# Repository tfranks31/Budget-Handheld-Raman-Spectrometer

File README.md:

# Budget-Handheld-Raman-Spectrometer
An inexpensive DIY handheld Raman spectrometer! Ever want to make a handheld Raman spectrometer for under $300?
Probably not! However, matter is just about everywhere and makes up most of everything. It would be cool to have a 
device that tells you what something is made out of, and would be even cooler to build it yourself!

This repository serves as the main repository for this project, and contains source code, electrical schematics, CAD 
models, future plans, and documentation for it all.

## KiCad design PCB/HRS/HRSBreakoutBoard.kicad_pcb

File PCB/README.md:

# PCB design and electrical schematics
Here exists all PCB designs and electrical schematics for the handheld Raman spectrometer project.

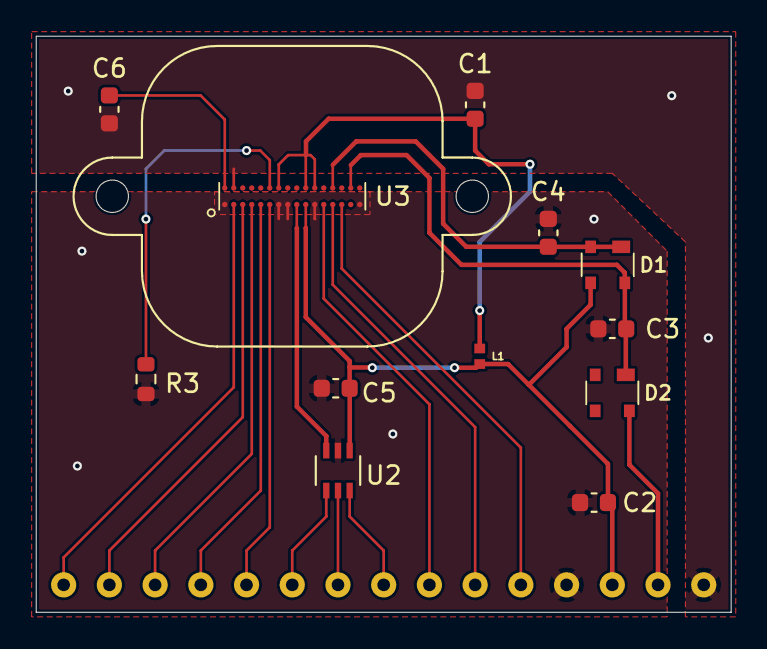
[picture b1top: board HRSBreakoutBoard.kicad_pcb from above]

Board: 2 copper layers, 38.6 x 32.0 mm, 13 parts (0 on the bottom side), 21 nets.

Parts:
C1, C2, C5, C6: 1.0uF; C_0603_1608Metric
C3, C4: 2.2uF; C_0603_1608Metric
D1, D2: BAT74,215; SOT143(B)
J1: Conn_01x15; Breakout Board Connector
L1: 600; BEADC1005X55N
R3: 56k; R_0603_1608Metric
U2: AD7476A; AD7476
U3: epc901; EPC901

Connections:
/AGND: C2.2, C3.1, C4.1, C5.1, J1.12, R3.2, U2.2 (GND), U3.1 (AGND), U3.7 (GND_OA), U3.8 (VIDEO_N), U3.11 (VIDEO_CM), U3.16 (AGND)
/CLR_DATA: J1.2, U3.3 (CLR_DATA)
/CLR_PIX: J1.4, U3.5 (CLR_PIX)
/DATA_RDY: J1.3, U3.4 (DATA_RDY)
/DGND: C1.1, C6.1, J1.15, U3.31 (DGND)
/PWR_DOWN: J1.1, U3.2 (PWR_DOWN)
/READ: J1.9, U3.12 (READ)
/SCL: J1.11, U3.14 (SCL)
/SCLK: J1.6, U2.4 (SCLK)
/SDA: J1.10, U3.13 (SDA)
/SDATA: J1.7, U2.5 (SDATA)
/SHUTTER: J1.5, U3.6 (SHUTTER)
/VDD: C1.2, L1.2, U3.22 (BW0), U3.23 (BW1), U3.26 (VDD)
/VDD_3V: C2.1, C5.2, D1.3, J1.13, L1.1, U2.1 (VDD), U3.10 (VDD_OA)
/VDD_5V: D2.4, J1.14
/VDD_5V0: C3.2, D1.4, D2.1, U3.18 (VDD_5V0)
/VDD_7V0: C4.2, D1.1, D1.2, U3.20 (VDD_7V0)
/VIDEO_P: U2.3 (VIN), U3.9 (VIDEO_P)
/~CS: J1.8, U2.6 (~CS)
unnamed: C6.2, U3.32 (VDD_1V8)
unnamed: R3.1, U3.27 (I_BIAS)

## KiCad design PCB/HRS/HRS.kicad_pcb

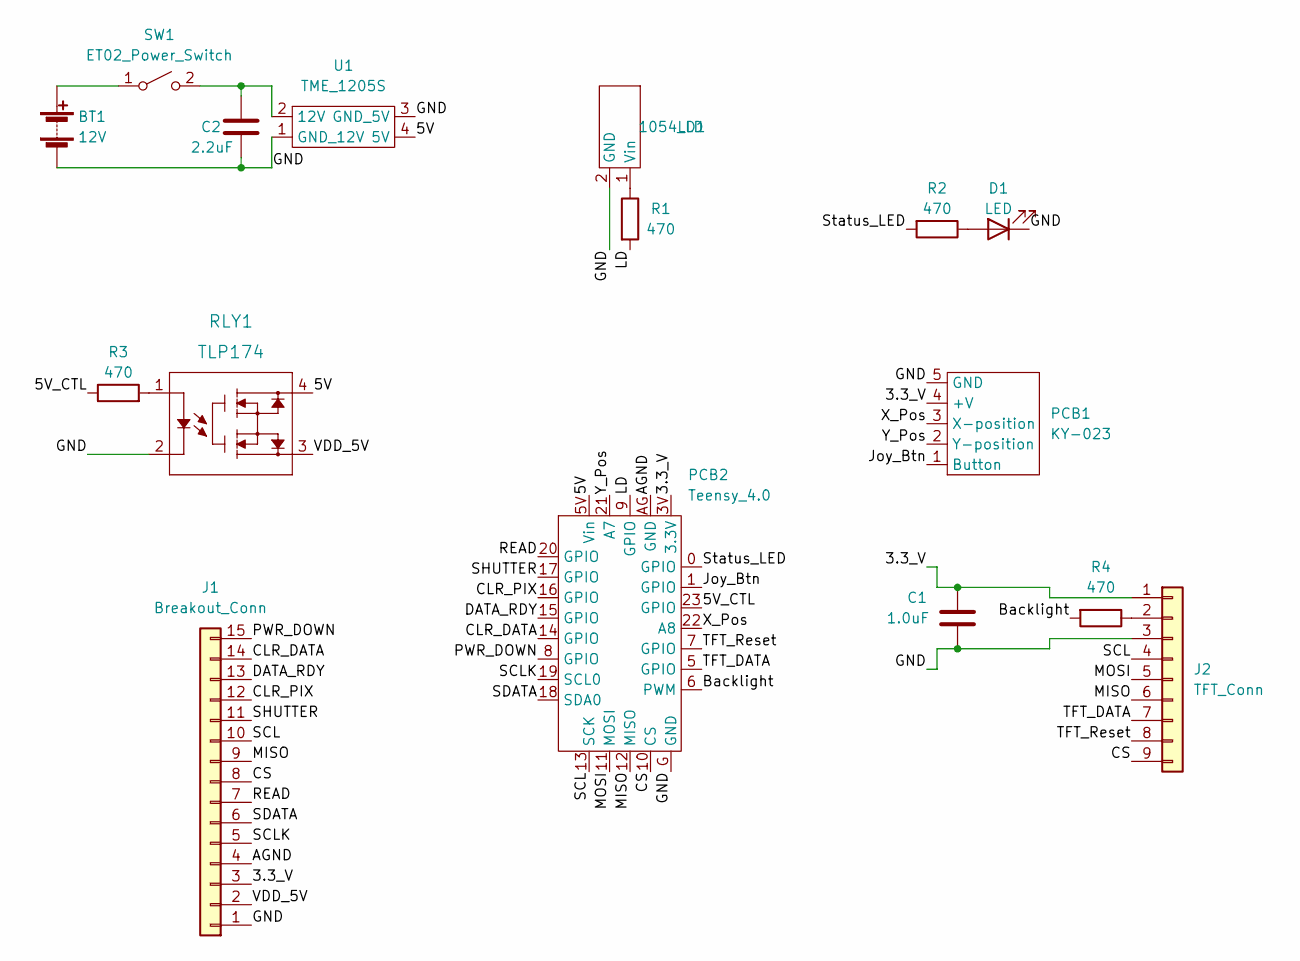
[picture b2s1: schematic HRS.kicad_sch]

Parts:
BT1: 12V; BAT&LD
C1: 1.0uF; C_0603_1608Metric
C2: 2.2uF; C_0603_1608Metric
D1: LED; LED_D5.0mm
J1: Breakout_Conn; Breakout-Connector-Female
J2: TFT_Conn
LD1: 1054_LD; BAT&LD
PCB1: KY-023; Ky-023
PCB2: Teensy_4.0; Teensy Headers
R1, R2, R3, R4: 470; R_0603_1608Metric
RLY1: TLP174
SW1: ET02_Power_Switch; ET02
U1: TME_1205S; TME 1205S

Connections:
/3.3_V: C1.2, J1.3, J2.1, PCB1.4 (+V), PCB2.3V (3.3V)
/5V: PCB2.5V (Vin), RLY1.4, U1.4 (5V)
/5V_CTL: PCB2.23 (GPIO), R3.1
/AGND: J1.4, PCB2.AG (GND)
/Backlight: PCB2.6 (PWM), R4.2
/CLR_DATA: J1.14, PCB2.14 (GPIO)
/CLR_PIX: J1.12, PCB2.16 (GPIO)
/CS: J1.8, J2.9, PCB2.10 (CS)
/DATA_RDY: J1.13, PCB2.15 (GPIO)
/GND: BT1.2 (-), C1.1, C2.1, D1.1 (K), J1.1, J2.3, LD1.2 (GND), PCB1.5 (GND), PCB2.G (GND), RLY1.2, U1.1 (GND_12V), U1.3 (GND_5V)
/Joy_Btn: PCB1.1 (Button), PCB2.1 (GPIO)
/LD: PCB2.9 (GPIO), R1.2
/MISO: J1.9, J2.6, PCB2.12 (MISO)
/MOSI: J2.5, PCB2.11 (MOSI)
/PWR_DOWN: J1.15, PCB2.8 (GPIO)
/READ: J1.7, PCB2.20 (GPIO)
/SCL: J1.10, J2.4, PCB2.13 (SCK)
/SCLK: J1.5, PCB2.19 (SCL0)
/SDATA: J1.6, PCB2.18 (SDA0)
/SHUTTER: J1.11, PCB2.17 (GPIO)
/Status_LED: PCB2.0 (GPIO), R2.2
/TFT_DATA: J2.7, PCB2.5 (GPIO)
/TFT_Reset: J2.8, PCB2.7 (GPIO)
/VDD_5V: J1.2, RLY1.3
/X_Pos: PCB1.3 (X-position), PCB2.22 (A8)
/Y_Pos: PCB1.2 (Y-position), PCB2.21 (A7)
unnamed: BT1.1 (+), SW1.1 (A)
unnamed: C2.2, SW1.2 (B), U1.2 (12V)
unnamed: D1.2 (A), R2.1
unnamed: J2.2, R4.1
unnamed: LD1.1 (Vin), R1.1
unnamed: R3.2, RLY1.1

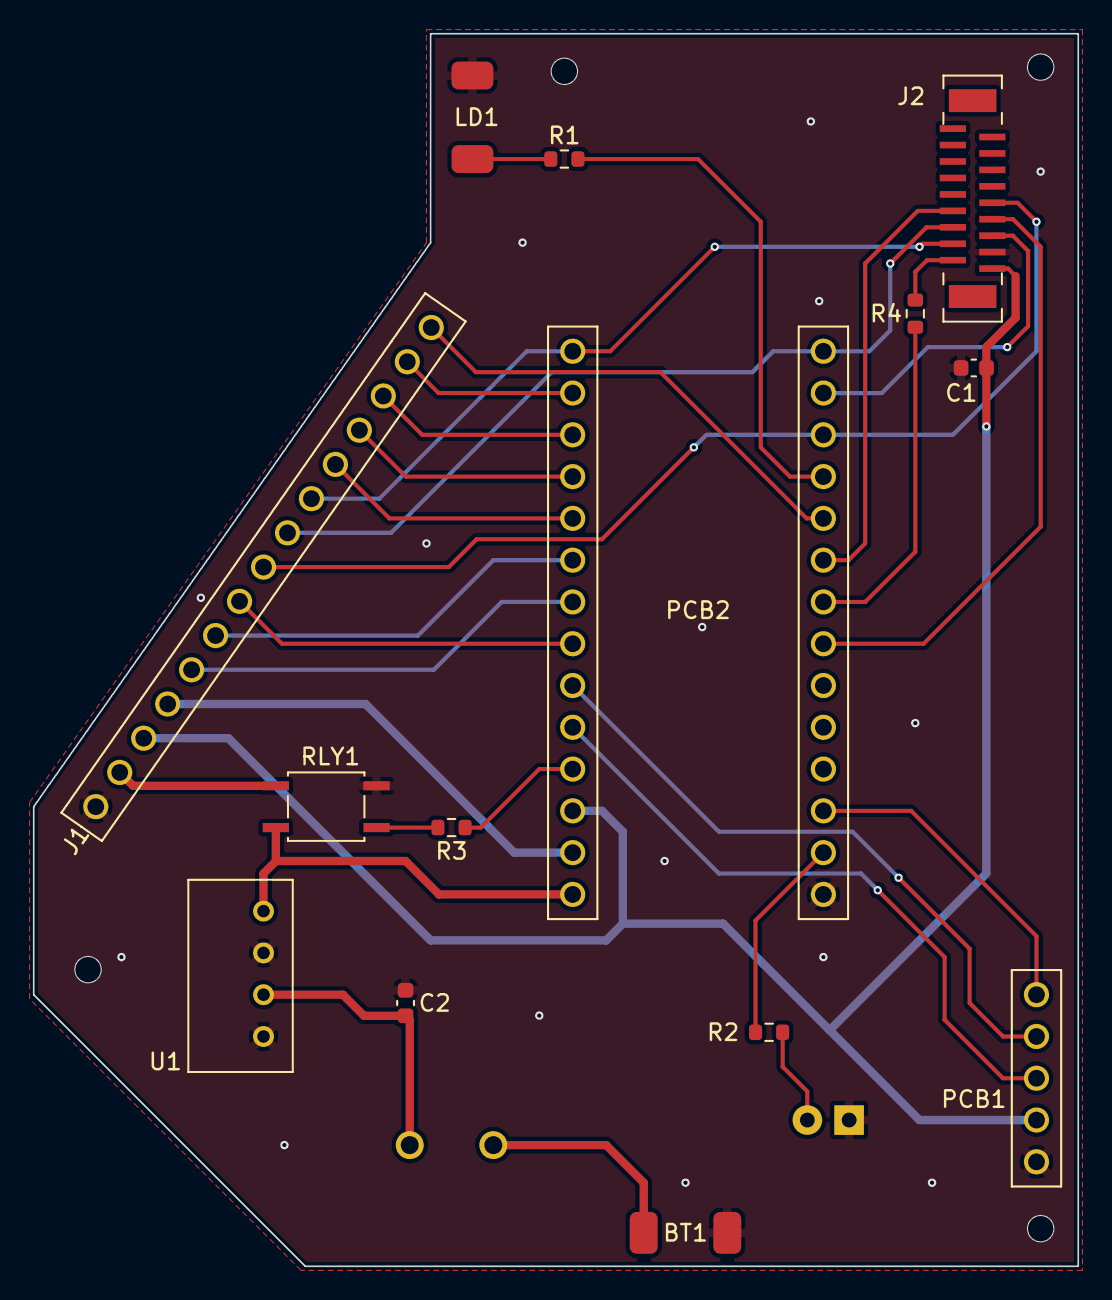
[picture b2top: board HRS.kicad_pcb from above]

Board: 2 copper layers, 63.5 x 74.9 mm, 16 parts (0 on the bottom side), 32 nets.

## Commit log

2022-06-08 Init
2022-06-08 Added READMEs to all folders to get them on Github
2022-06-13 Added more datasheets and created Platform.io framework
2022-06-14 Added tft libraries and workspace settings
2022-06-26 Added schematics and symbols for pcb
2022-07-02 Completed footprints and schematics
2022-07-03 Added resistor for TFT backlight
2022-07-03 Created led module header
2022-07-03 Created and implemented led module
2022-07-03 Renamed LED files and created LEDController files
2022-07-03 Created LEDController header file
2022-07-04 Started LED modes and created mode enum and timer
2022-07-04 Created all led module functionality
2022-07-04 Finished LED module
2022-07-04 Make led fade rate faster
2022-07-08 Made PCBs
2022-07-08 Added laser module class
2022-07-08 Created laser module cpp
2022-07-09 Created LaserController header
2022-07-09 Created LaserController implementation
2022-07-09 Added bring online and offline functionality to LaserController
2022-07-09 Forgot to save and include bringOffline()
2022-07-09 Created joystick header
2022-07-09 Created joystick module implementation
2022-07-09 Added interrupt for button press and moved clearButtonPress
2022-07-10 Created joystick controller header
2022-07-10 Created JoystickController and made minor fixes
2022-07-10 Created button press timer to ignore bounces
2022-07-10 Fixed joystick directions
2022-07-10 Fixed comments and created constant
2022-07-17 ms2 demo
2022-07-17 Added relay header
2022-07-17 Created relay module implementation
2022-07-17 Removed redundant isOn
2022-07-17 Created relay controller header
2022-07-18 Implemented relay controller
2022-07-18 Added CAD models for testing
